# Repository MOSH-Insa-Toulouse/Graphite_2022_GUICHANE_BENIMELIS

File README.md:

# Graphite_2022_GUICHANE_BENIMELIS
Projet "Capteur de Graphite", dans le contexte de l'UF **"Du capteur au banc de test"**, département de Génie Physique de l'INSA Toulouse.
***
L'objectif de ce projet est de reprendre les recherches scientifiques sur un capteur low-tech, le **"Pencil Draw Strain Gauges"**. Le fonctionnement de ce capteur est simple. Il suffit de dessiner au crayon à papier sur une feuille et d'appliquer ensuite une contrainte sur celle-ci. La contrainte appliquée va modifier la distance entre les particules de graphique et par conséquent la résistance au passage du courant. Nous avons donc notre capteur. 

Nous avons donc décidé de fabriquer nous-même ce capteur et de le tester. Les étapes et le matériel nécessaire à cette réalisation son détaillés ci-dessous. 

## Sommaire
* [1. Livrables](#PremiereSection)
* [2. Matériel nécessaire](#DeuxiemeSection)
* [3. Simulation sous LTspice](#TroisiemeSection)
* [4. Code Arduino](#SeptiemeSection)
* [5. Application Android](#QuatriemeSection)
* [6. KICAD](#CinquiemeSection)
  * [6.1. Les composants](#CinquiemeSection1)
  * [6.2. La schématique](#CinquiemeSection2)
  * [6.3. Le placement des composants](#CinquiemeSection3)
  * [6.4. La visualisation 3D](#CinquiemeSection4)
* [7. Fabrication du PCB designer sur KICAD](#SixiemeSection)
* [8. Banc de test](#HuigtiemeSection)
  * [8.1. Création du banc](#HuigtiemeSection1)
  * [8.2. Tests effectués](#HuigtiemeSection2)
* [9. Datasheet](#NeuviemeSection)
* [Contacts](#DixiemeSection)

## 1. Livrables 
Ce projet sera évalué au sein de l'UF **"Du capteur au banc de test"**. 
Nous sommes donc amenés à rendre tout un ensemble de livrables que voici:
- Un **code Arduino** permettant de mesurer la déformation du capteur et de piloter à minima un module bluetooth, un encodeur rotatoire et un écran OLED
- Une **carte PCB** se connectant au module **Arduino UNO** contenant à minima un amplificateur transimpédance, un module bluetooth, un écran OLED et un encodeur rotatoire
- Une **application Android APK**
- Une **simulation sous LTspice**
- Un **banc de test** 
- La **datasheet** du capteur de déformation

## 2. Matériel nécessaire
Afin de mener à bien ce projet nous avons eu besoin de: 

* 2 résistance 100kΩ
* 2 résistance 1kΩ
* 1 résistance 10kΩ
* 1 capacité 1μF
* 3 capacité 100nF
* 1 amplificateur opérationnel LTC1050
* 1 module Bluetooth HC05
* 1 écran OLED I2C 0.91
* 1 encodeur rotatoire KY_040
* une feuille de papier avec du graphite (crayon à papier) comme ci-dessous

## 3. Simulation Sous LTspice 
Le capteur de graphite que nous voulons créer délivre un signal de courant très faible, d'environ 100 nA. Le microcontroleur ne peut donc pas mesurer directement ce courant. Nous choisissons donc d'utiliser un amplificateur transimpédance pour convertir une variation de courant en variation de tension et l'amplifier, suivi de plusieurs filtres afin que ce faible signal ne soit pas perturbé par le bruit.

Voici le schéma que nous avons réalisé:
<p align="center">

<p/>

Voici les fonctionnalités des différents composants: 
- R5 protège l'amplificateur opérationnel contre les décharges électrostatiques, avec C1 forme un filtre pour les bruits en tension
- C1 avec R1 forment un filtre pour le bruit en courant 
- R2 est interchangeable pour permettre une adaptation du calibre
- C4 avec R3 forment un filtre actif
- C2 avec R6 forment un filtre de sortie 
- C3 filtre le bruit de l'alimentation

Nous avons simulé notre circuit dans les **conditions nominales**. Voici la réponse de notre circuit:

Le capteur est fonctionnel et ne sature pas car la hauteur du plateau est à 1V (inférieur à 5V).

La datasheet de l'amplificateur LTC1050C nous indique que sa **tension d'offset** est de l'ordre 5 µV et que le **maximum d’offset de décalage** est de l’ordre se 0,05µV/°C. Ces valeurs nous semblent acceptables car nous mesurons une tension de 10 mV aux bornes de R1. Cette valeur est 2000 fois supérieure à la tension d’offset de l’amplificateur. Nous pouvons donc choisir cet amplificateur sans problème.

De même le **courant d’offset** indiqué dans la datasheet est de 160 pA. Cette valeur semble acceptable devant le courant circulant dans R1 par exemple qui est de l’ordre de 100 nA. Cette valeur est 625 fois supérieure à la tension d’offset qu’on peut donc négliger. 

Nous devons aussi prendre en compte les caractéristiques de la carte Arduino que nous utilisons:
- Résolution: 10-13 bits
- Vref: 1,1V to 5,0V
- Impédence maximale: 1kOhm-10kOhm
- Fréquence d'échantillonage max: 15kHz

Nous utilisons l'Arduinon Uno à sa fréquence max (15kHz). La **limite de repliement** autrement appelée fréquence de Nyquist, est égale à la moitié de la fréquence d'échantillonage choisie, ici 15kHz, soit à 7,5kHz. Sur la simulation ci-dessous, on peut voir qu'à une fréquence de 7,5kHz, on a un gain d'environ 30db. On peut donc déduire que l'attétuation est d'environ 110dB. 

Nous avons ensuite calculé les **fréquences de courpure des différents filtres**:
- Filtre d'entrée (R5 associée à C1) 

On obtient à -3dB, une fréquence de coupure de 20Hz ce qui fonctionne bien pour l'entrée du capteur. 

- Filtre actif (R3 associée à C4) 

On obtient à -3dB, une fréquence de coupure de 2Hz qui permet de couper le bruit induit par le secteur 50Hz.

- Filtre de sortie (R6 associée à C2) 

On obtient à -3dB, une fréquence de coupure de 1,5kHz ce qui fonctionne bien pour l'échantillonage de l'ARDUINO.

En faisant varier C1, nous avons pu observer l'infuence de cette capacité sur **l'atténuation globale d'un bruit de courant de 50Hz**. 
- C1= 1u:

-C1=100n:

## 4. Code Arduino  

L’objectif de ce projet est de mesurer une valeur de résistance. La première étape du code est donc de lire cette valeur. C’est pourquoi nous utilisons la fonction getResistance(int pin) qui permet de lire une valeur analogique sur le pin A0. Cette valeur est ensuite convertie en tension. Nous relions la valeur de la tension de sortie à la résistance en entrée du circuit.

Une fois cette valeur récupérée, il faut l’afficher sur un écran OLED. Nous avons réfléchi à un menu que nous pourrions actualiser à l’aide d’un encodeur rotatoire.

Notre menu est défini par une fonction updateMenu() dans lequel 4 cas sont observés. Le premier correspond à l'affichage de la résistance, le second de la date, le troisième de l’heure et le dernier est un mini jeu que nous détaillerons plus tard. Pour chaque « case » du menu, une action différente est effectuée. 

L’encodeur rotatoire va avoir un rôle à jouer dans la sélection et l’affichage de ces fonctions. En effet, nous lions les pins CLK et SW de l’encodeur à la commande attachInterrupt(pin, fonction(), état). Chaque fois que l’état est déclenché, fonction() est appelée. Chaque fois que l’état du pin CLK passe de 0 à 1, la fonction doEncoder est appelée. Cette fonction incrémente la variable « menu » qui permet de choisir un des cas observés précédemment. De même, chaque fois que l’état de SW change, la fonction Action() est appelée. Cette fonction commande la variable « menuState » aux valeurs 1 et 0. Lorsque « menuState » == 0, la boucle loop() met à jour le menu en appelant updateMenu(). Lorsque « menuState » == 1, la boucle loop() rentre dans un des choix du menu en appelant executeAction(). 

La fonction graphique est un mini-jeu dont le but est d’aller d’un bout à l’autre de l’écran. On redimensionne la valeur de la résistance sur l’écran OLED puis on augmente ou diminue la résistance pour aller plus haut ou plus bas et esquiver les traits bleus sur le chemin. Si nous touchons une ligne, nous avons perdu.

Pour finir, nous ajoutons le module Bluetooth. Par l’intermédiaire de ce module, nous envoyons la valeur de la résistance à l’application créée sur MIT App Inventor.

## 5. Application Android 
Nous avons ensuite cherché à afficher les valeurs de résistance du capteur sur un téléphone mobile Android. Pour cela nous avons crée une application grâce au site MIT App Inventor. 
Notre interface comprend:
- Un bouton de connexion au bluetooth qui devient vert quand la connexion est établie ou rouge quand elle ne l'est pas
- Un menu déroulant qui permet de choisir ce que l'on veut afficher (valeur de la résistance, graphe de la résistance en fonction du temps ou les deux)
- La valeur de la résistance du capteur de graphène
- Un graphe où s'affiche le tracé de la résistance du capteur en fonction du temps
- Un bouton "Reset" qui permet d'effacer le graphe 
- Une information sur les bits contenus dans le buffer

## 6. KICAD 
Nous avons modélisé notre shield PCB sur le logiciel KICAD. Pour cela nous avons **designé tous les composants du PCB et créé leur empreinte** (l'aplificateur, l'écran OLED, le module Bluetooth et l'encodeur rotatoire). Nous avons ensuite créé les **connexions** entre tous les composants et avec la carte Arduino sur le logiciel. Enfin nous avons **modélisé la carte PCB** et créé un **modèle 3D** de l'ensemble. 
### 6.1. Les composants 
* L'amplificateur LTC1050

* L'écran OLED

* L'encodeur rotatoire KY_040

* Le module bluetooth HC05

### 6.2. Schématique 
Une fois les composants créés nous les relions entre eux et avec les broches de la carte Arduino. 

### 6.3. Placement des composants 
Nous plaçons ensuite les composants sur le shield et traçons les connexions de sorte que les fils ne se croisent pas. 

### 6.4. Visualisation 3D 
Nous avons, enfin, téléchargé les modèles 3D de nos composants afin de visualiser notre PCB en 3D. Cela nous permet aussi d'effectuer une dernière vérification et de voir qu'aucuns composants ne se chevauchent. 
<p align="center">

<p/>

## 7. Fabrication du shield 

Avec l'aide de Catherine Crouzet, nous avons réalisé le PCB à partir d'une plaquette d'époxy recouverte d'une fine couche de cuivre.
Premièrement nous avons imprimé la modélisation du PCB que nous avions faite sur le logiciel KICAD. Cela joue le rôle de masque lors de l'insolation de la plaquette sous UVs. A l'aide d'unrévélateur nous retirons la partie de la résine qui n'a pas été insolée. Ensuite, la plaquette est placée dans un bain de perchlorure de fer pour la gravure. Le cuivre non protégé par la résine s'enlève et nous obtenons le PCB tel que nous l'avions designé sur KICAD. 
Pour éliminer les dernières traces de résine, on lave le PCB à l'acétone. 
<p align="center">
 
<p/>

Nous avons ensuite percé notre PCB afin d'y insérer les différents composants. Le diamètre des trous varie selon les composants à placer :
* ⌀ 0.8mm : pour l'Amplificateur LTC1050, les résistances et les capacités
* ⌀ 1.0mm : Pour les broches de connexion de la carte Arduino Uno et les différents modules (OLED, bluetooth, encodeur rotatoire)

## 8. Banc de test  
### 8.1. Banc de test  
Nous avons imaginé un banc de test afin de pouvoir tester notre capteur. Nous utilisons un rail sur lequel nous rajoutons deux supports. Entre ces-derniers nous mettrons notre capteur sur une réglette flexible. En faisant varier la distance entre les deux supports, la réglette flexible se courbe. Nous relevons cette courbure et la résistance du capteur associée.
Nous avons imprimé deux pièces 3D afin de réaliser ce banc de test. Ce sont des supports pour la réglette flexible. La partie arrière est légèrement inclinée afin que la réglette ne parte pas lors de la flexion.  

### 8.2. Résultats obtenus  
Nous avons fait plusieurs mesures en flexion, en donnant à notre capteur une forme concave puis convexe. Nous utilisons un crayon a papier de type critérium avec une mine HB.

On remarque que la résistance diminue lorsqu'on donne une forme convexe à notre capteur et inversement pour le cas concave. Cela est dû au rapprochement ou à l'éloignement des molécules de graphite comme nous l'expliquions plus au plus haut. 

## 9. Datasheet  
A l'aide de nos résultats obtenus lors de nos essais avec le banc de test, nous avons pu mettre au point une datasheet de notre capteur. Celle-ci se trouve dans les fichiers à télécharger. 

## Contacts  
Pour toutes questions n'hésitez pas à nous contacter !
* Marie Bénimélis : benimeli@insa-toulouse.fr
* Mathys Guichané : guichane@insa-toulouse.fr

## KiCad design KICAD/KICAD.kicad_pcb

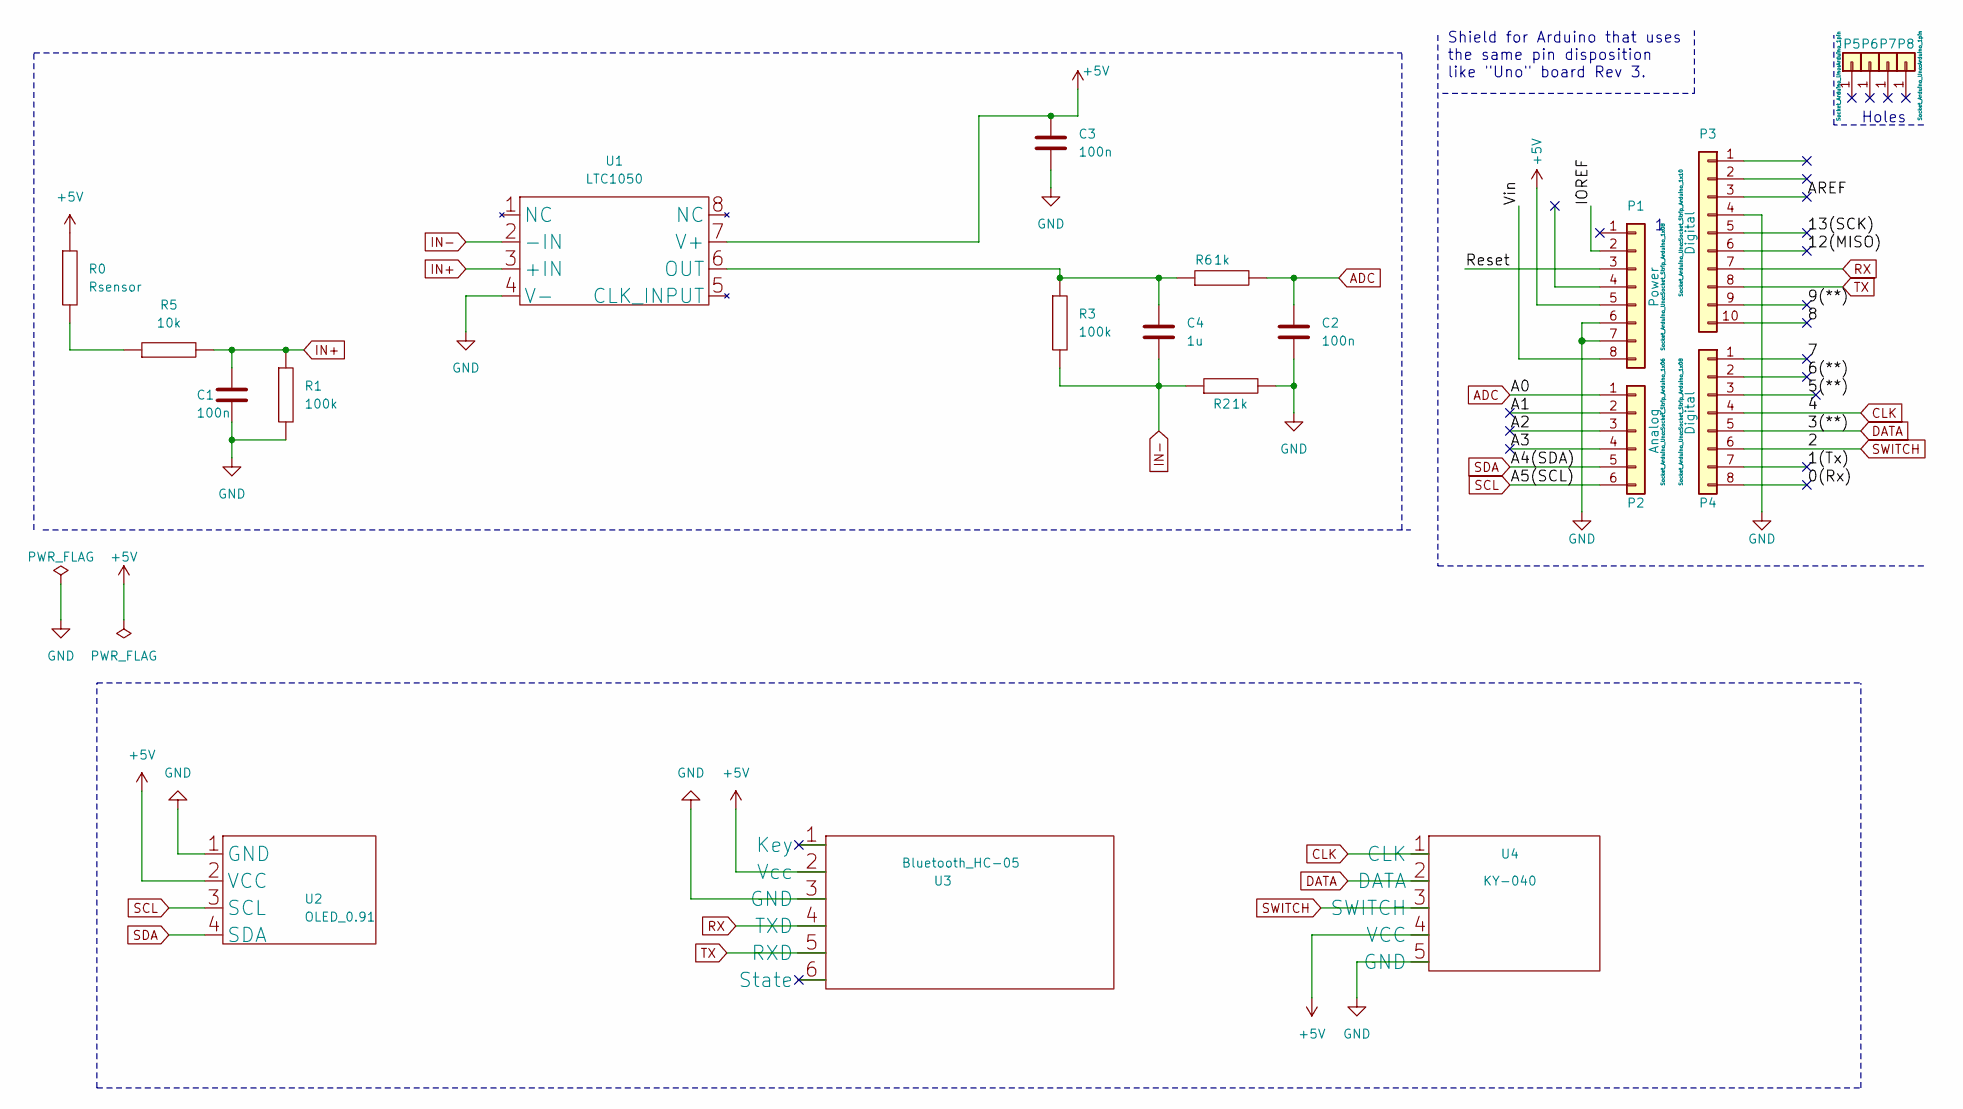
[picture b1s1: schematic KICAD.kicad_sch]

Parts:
C1, C2, C3: 100n; C_Disc_D7.0mm_W2.5mm_P5.00mm
C4: 1u; C_Rect_L7.0mm_W2.0mm_P5.00mm
P1: Power; Socket_Strip_Arduino_1x08
P2: Analog; Socket_Strip_Arduino_1x06
P3: Digital; Socket_Strip_Arduino_1x10
P4: Digital; Socket_Strip_Arduino_1x08
P5, P6, P7, P8: CONN_01X01; Arduino_1pin
R0: Rsensor; R_Axial_DIN0207_L6.3mm_D2.5mm_P7.62mm_Horizontal
R1, R3: 100k; R_Axial_DIN0207_L6.3mm_D2.5mm_P10.16mm_Horizontal
R2, R6: 1k; R_Axial_DIN0207_L6.3mm_D2.5mm_P7.62mm_Horizontal
R5: 10k; R_Axial_DIN0207_L6.3mm_D2.5mm_P10.16mm_Horizontal
U1: LTC1050; DIP-8_296_ELL
U2: OLED_0.91; SIP-4
U3: Bluetooth_HC-05; SIP-6
U4: KY-040; SIP-5

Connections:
+5V: C3.1, P1.5, R0.1, U1.7 (V+), U2.2 (VCC), U3.2 (Vcc), U4.4 (VCC)
/0(Rx): P4.8
/1(Tx): P4.7
/5(**): P4.3
/6(**): P4.2
/7: P4.1
/8: P3.10
/9(**): P3.9
/12(MISO): P3.6
/13(SCK): P3.5
/A1: P2.2
/A2: P2.3
/A3: P2.4
/AREF: P3.3
/IOREF: P1.2
/Reset: P1.3
/Vin: P1.8
ADC: C2.1, P2.1, R6.2
CLK: P4.4, U4.1 (CLK)
DATA: P4.5, U4.2 (DATA)
GND: C1.2, C2.2, C3.2, P1.6, P1.7, P3.4, R1.2, R2.2, U1.4 (V-), U2.1 (GND), U3.3 (GND), U4.5 (GND)
IN+: C1.1, R1.1, R5.2, U1.3 (+IN)
IN-: C4.2, R2.1, R3.2, U1.2 (-IN)
unnamed: C4.1, R3.1, R6.1, U1.6 (OUT)
unnamed: R0.2, R5.1
RX: P3.7, U3.4 (TXD)
SCL: P2.6, U2.3 (SCL)
SDA: P2.5, U2.4 (SDA)
SWITCH: P4.6, U4.3 (SWITCH)
TX: P3.8, U3.5 (RXD)

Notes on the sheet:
Holes
Shield for Arduino that uses the same pin disposition like "Uno" board Rev 3.

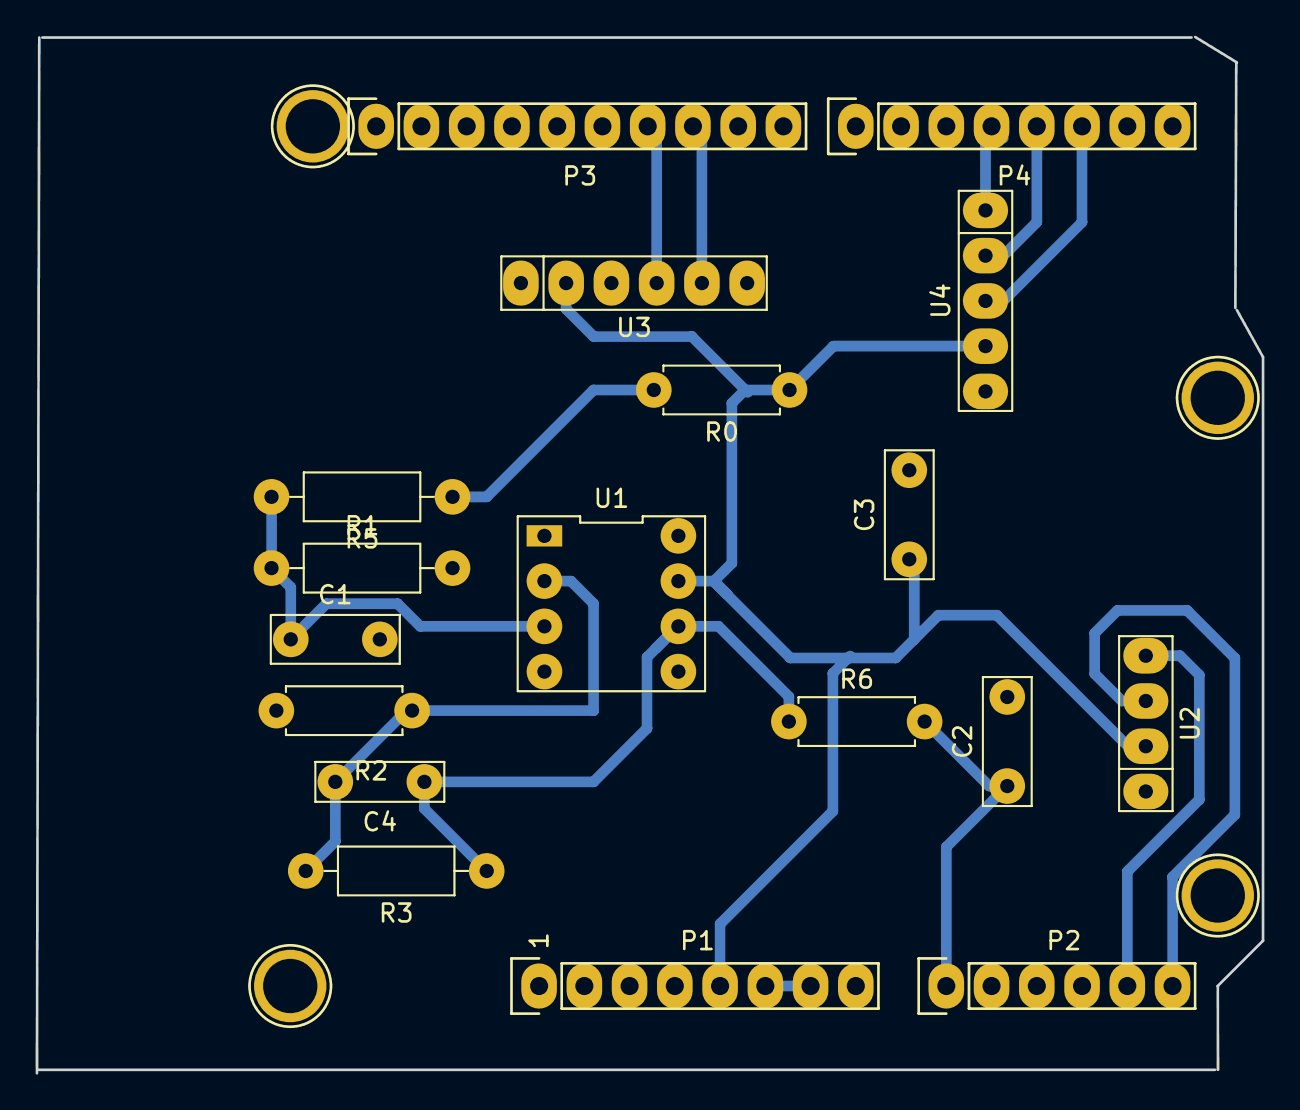
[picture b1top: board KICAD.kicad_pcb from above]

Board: 2 copper layers, 68.8 x 58.2 mm, 22 parts (0 on the bottom side), 14 nets.
